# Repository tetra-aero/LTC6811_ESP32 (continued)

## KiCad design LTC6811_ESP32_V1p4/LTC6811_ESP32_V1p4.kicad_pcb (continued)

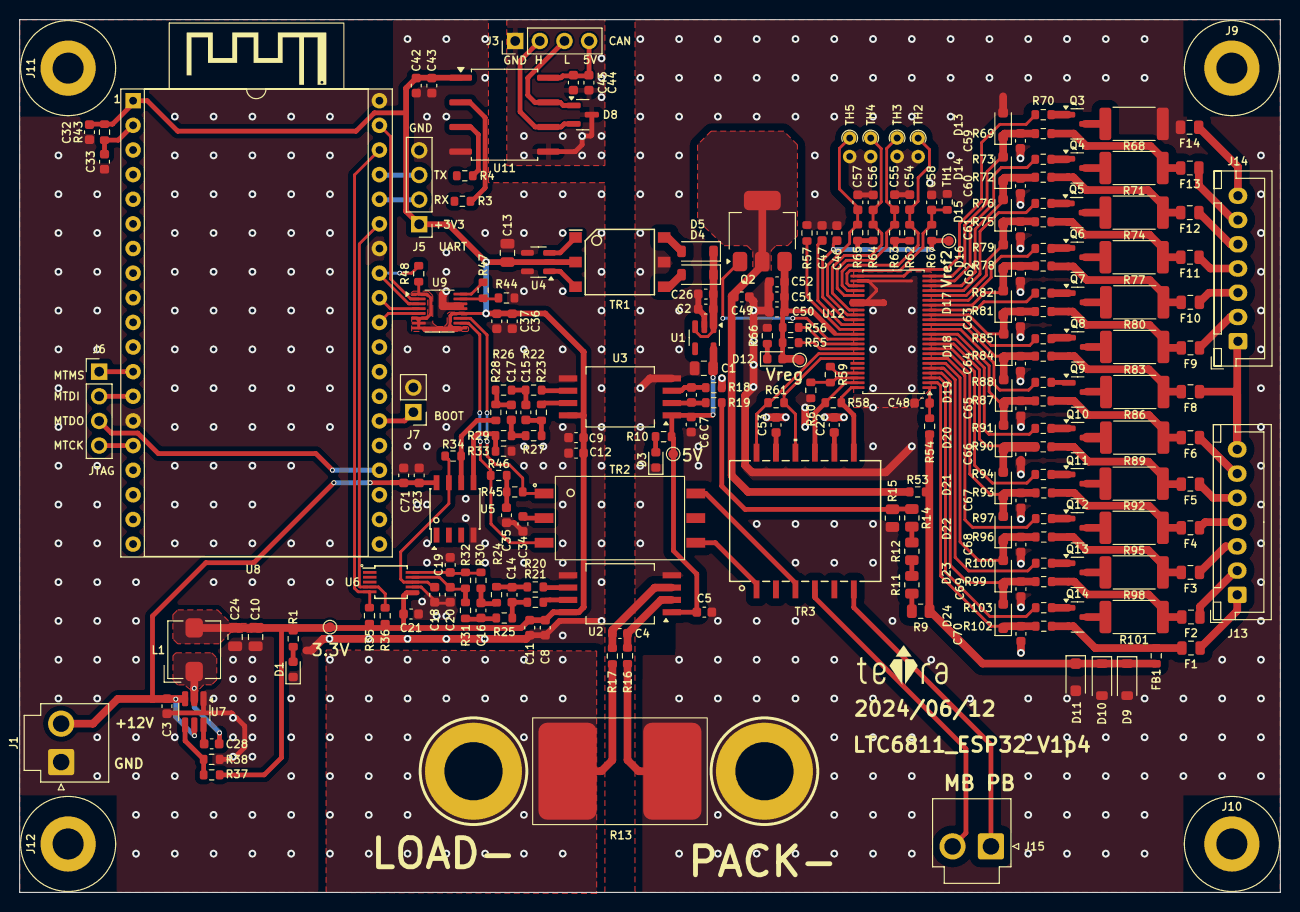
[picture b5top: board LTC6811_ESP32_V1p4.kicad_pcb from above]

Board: 2 copper layers, 130.0 x 90.0 mm, 239 parts (0 on the bottom side), 168 nets.

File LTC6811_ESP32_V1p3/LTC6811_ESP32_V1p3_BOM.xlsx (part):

LTC6811_ESP32_V1p3 BOM
 | Reference | Value | Footprint | Datasheet | Description | Link | MPN | Quantity
1 | BZ1 | AI-1027-TWT-5V | Buzzer_Beeper:Beeper_AI-1027-TWT-5V | https://www.puiaudio.com/media/SpecSheet/AI-1027-TWT-5V-2-R.pdf | Buzzers Indicator, Internally Driven Electromechanical/Magnetic 5 V 30mA 2.73kH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 | https://www.digikey.jp/en/products/detail/pui-audio-inc/AI-1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 | AI-1027-TWT-5V-2-R | 1
2 | C1, C10, C13, C24, C27 | 10uF/16V | Capacitor_SMD:C_0805_2012Metric | https://mm.digikey.com/Volume0/opasdata/d220001/medias/docus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 | 10 uF ±10% 16V Ceramic Capacitor X5R 0805 (2012 Metric) | https://www.digikey.jp/en/products/detail/samsung-electro-me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 | CL21A106KOQNNNE | 5
3 | C2, C5, C6, C8, C9, C18-C21, C23, C25, C28, C32, C33, C37, C40, C48, C49, C54-C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 | 100nF/100V | Capacitor_SMD:C_0603_1608Metric | https://www.digikey.jp/en/products/detail/samsung-electro-me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 | 0.1 uF ±10% 100V Ceramic Capacitor X7R 0603 (1608 Metric) | https://www.digikey.jp/en/products/detail/samsung-electro-me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 | CL10B104KC8NNNC | 35
4 | C3, C11, C12, C38, C41 | 2.2uF/25V | Capacitor_SMD:C_0603_1608Metric | https://search.murata.co.jp/Ceramy/image/img/A01X/G101/ENG/G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 | 2.2 uF ±10% 25V Ceramic Capacitor X5R 0603 (1608 Metric) | https://www.digikey.jp/en/products/detail/murata-electronics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 | GRM188R61E225KA12D | 5
5 | C4, C7 | 330pF/100V | Capacitor_SMD:C_0603_1608Metric | https://datasheets.kyocera-avx.com/KGM_X7R.pdf | 330 pF ±10% 100V Ceramic Capacitor X7R 0603 (1608 Metric) | https://www.digikey.jp/en/products/detail/kyocera-avx/KGM15A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 | GRM188R72A331KA01D | 2
6 | C14, C15 | 2.2nF/16V | Capacitor_SMD:C_0603_1608Metric | https://connect.kemet.com:7667/gateway/IntelliData-Component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 | 2200 pF ±10% 16V Ceramic Capacitor X7R 0603 (1608 Metric) | https://www.digikey.jp/en/products/detail/kemet/C0603C222K4R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 | C0603C222K4RECAUTO | 2
7 | C16, C17 | 220pF/50V | Capacitor_SMD:C_0603_1608Metric | https://search.murata.co.jp/Ceramy/image/img/A01X/G101/ENG/G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 | 220 pF ±5% 50V Ceramic Capacitor C0G, NP0 0603 (1608 Metric) | https://www.digikey.jp/en/products/detail/murata-electronics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 | GCM1885C1H221JA16D | 2
8 | C22, C53 | 100pF/100V | Capacitor_SMD:C_0603_1608Metric | https://search.murata.co.jp/Ceramy/image/img/A01X/G101/ENG/G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 | 100 pF ±10% 100V Ceramic Capacitor X7R 0603 (1608 Metric) | https://www.digikey.jp/en/products/detail/murata-electronics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 | 0603B101K101SD | 2
9 | C26, C39 | 4.7uF/16V | Capacitor_SMD:C_0603_1608Metric | https://mm.digikey.com/Volume0/opasdata/d220001/medias/docus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 | 4.7 uF ±10% 16V Ceramic Capacitor X5R 0603 (1608 Metric) | https://www.digikey.jp/en/products/detail/samsung-electro-me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 | CL10A475KO8NNNC | 2
10 | C34, C35 | 10nF/100V | Capacitor_SMD:C_0603_1608Metric | https://search.murata.co.jp/Ceramy/image/img/A01X/G101/ENG/G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 | 10000 pF ±10% 100V Ceramic Capacitor X7R 0603 (1608 Metric) | https://www.digikey.jp/en/products/detail/murata-electronics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 | GCM188R72A103KA37D | 2
11 | C36, C46, C47, C50-C52, C71 | 1uF/25V | Capacitor_SMD:C_0603_1608Metric | https://mm.digikey.com/Volume0/opasdata/d220001/medias/docus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 | 1 uF ±10% 25V Ceramic Capacitor X7R 0603 (1608 Metric) | https://www.digikey.jp/en/products/detail/samsung-electro-me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 | 0603B105K250XD | 7
12 | D1-D3, D12 | LED Red | LED_SMD:LED_0603_1608Metric | https://optoelectronics.liteon.com/upload/download/DS-22-99-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 | Red 631nm LED Indication - Discrete 2V 0603 (1608 Metric) | https://www.digikey.jp/en/products/detail/liteon/LTST-C190KR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 | LTST-C190KRKT | 4
13 | D4, D5 | MBR0520 | Diode_SMD:D_SOD-123 | http://www.mccsemi.com/up_pdf/MBR0520~MBR0580(SOD123).pdf | Diode 20 V 500mA Surface Mount SOD-123 | https://www.digikey.jp/en/products/detail/micro-commercial-c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 | MBR0520-TP | 2
14 | D7 | ESD24VS2U | Package_TO_SOT_SMD:SOT-23 | https://www.infineon.com/dgdl/Infineon-ESD24VS2U-DS-v01_01-e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 | 41V Clamp 5A (8/20us) Ipp Tvs Diode Surface Mount PG-SOT23 | https://www.digikey.jp/en/products/detail/infineon-technolog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 | ESD24VS2UE6327HTSA1 | 1
15 | D9, D10 | 1N4148W | Diode_SMD:D_SOD-123 | https://www.diodes.com/assets/Datasheets/BAV16W_1N4148W.pdf | Diode 100 V 300mA Surface Mount SOD-123 | https://www.digikey.jp/en/products/detail/diodes-incorporate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 | 1N4148W-7-F | 2
16 | D11 | BZT52H-C62 | Diode_SMD:D_SOD-123F | https://assets.nexperia.com/documents/data-sheet/BZT52H_SER.pdf | Zener Diode 62 V 375 mW ±5% Surface Mount SOD-123F | https://www.digikey.jp/en/products/detail/nexperia-usa-inc/B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 | BZT52H-C62,115 | 1
17 | D13-D24 | PDZ7.5B | Diode_SMD:D_SOD-323_HandSoldering | https://assets.nexperia.com/documents/data-sheet/PDZ-B_SER.pdf | Zener Diode 7.6 V 400 mW ±2% Surface Mount SOD-323 | https://www.digikey.jp/en/products/detail/nexperia-usa-inc/P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 | PDZ7.5BZ | 12
18 | F1-F6, F8-F14 | MPZ2012S102ATD25 | Fuse:Fuse_0805_2012Metric | https://product.tdk.com/en/system/files?file=dam/doc/product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 | 1 kOhms @ 100 MHz 1 Power Line Ferrite Bead 0805 (2012 Metric) 1.5A 150mOhm | https://www.digikey.jp/en/products/detail/tdk-corporation/MP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 | MPZ2012S102ATD25 | 13
19 | FB1 | BLM18PG330SN1D | Resistor_SMD:R_0603_1608Metric | https://www.murata.com/en-us/products/productdata/8796738650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 | 33 Ohms @ 100 MHz 1 Power Line Ferrite Bead 0603 (1608 Metric) 3A 25mOhm | https://www.digikey.jp/en/products/detail/murata-electronics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 | BLM18PG330SN1D | 1
20 | J1, J15 | PB MB | Connector_JST:JST_VH_B2P-VH-B_1x02_P3.96mm_Vertical | https://www.jst-mfg.com/product/pdf/eng/eVH.pdf | Connector Header Through Hole 2 position 0.156" (3.96mm) | https://www.digikey.jp/en/products/detail/jst-sales-america-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 | B2P-VH | 2
21 | J4 | USB | Connector_USB:Micro_USB_B-2013499-1 | chrome-extension://efaidnbmnnnibpcajpcglclefindmkaj/https://www.te.com/usa-en/p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 | USB - micro B USB 2.0 Receptacle Connector 5 Position Surface Mount, Right Angl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 | https://www.digikey.jp/en/products/detail/te-connectivity-am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 | 2013499-1 | 1
22 | J13, J14 | B7B-XH-A | Connector_JST:JST_XH_B7B-XH-A_1x07_P2.50mm_Vertical_BAT_6S | https://www.jst-mfg.com/product/pdf/eng/eXH.pdf | Connector Header Through Hole 7 position 0.098" (2.50mm) | https://www.digikey.jp/en/products/detail/jst-sales-america-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 | B7B-XH-A | 2
23 | L1 | 3.3uH | Inductor_SMD:L_Bourns_SRP5030T | https://www.bourns.com/docs/Product-Datasheets/SRP5030CC.pdf | 3.3 uH Shielded Wirewound Inductor 5 A 38mOhm Max Nonstandard | https://www.digikey.jp/en/products/detail/bourns-inc/SRP5030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 | SRP5030CC-3R3M | 1
24 | Q1 | BSS138 | Package_TO_SOT_SMD:SOT-23 | https://mm.digikey.com/Volume0/opasdata/d220001/medias/docus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 | N-Channel 50 V 220mA (Ta) 350mW (Ta) Surface Mount SOT-23 | https://www.digikey.jp/en/products/detail/anbon-semiconducto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 | BSS138 | 1
25 | Q2 | NSV1C201MZ4 | Package_TO_SOT_SMD:SOT-223 | https://www.onsemi.com/pdf/datasheet/nss1c201mz4-d.pdf | Bipolar (BJT) Transistor NPN 100 V 2 A 100MHz 800 mW Surface Mount SOT-223 (TO-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 | https://www.digikey.jp/en/products/detail/onsemi/NSV1C201MZ4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 | NSV1C201MZ4T1G | 1
26 | Q3-Q14 | TSM2323 | Package_TO_SOT_SMD:SOT-23 | https://www.taiwansemi.com/assets/uploads/datasheet/TSM2323_F15.pdf | P-Channel 20 V 4.7A (Ta) 1.25W (Ta) Surface Mount SOT-23 | https://www.digikey.jp/en/products/detail/taiwan-semiconduct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 | TSM2323CX RFG | 12
27 | R1, R2, R10 | 470R | Resistor_SMD:R_0603_1608Metric | https://www.yageo.com/upload/media/product/products/datashee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 | 470 Ohms ±5% 0.1W, 1/10W Chip Resistor 0603 (1608 Metric) Moisture Resistant Th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 | https://www.digikey.jp/en/products/detail/yageo/RC0603JR-074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 | RC0603JR-07470RL | 3
28 | R5 | 1.5K | Resistor_SMD:R_0603_1608Metric | https://www.yageo.com/upload/media/product/products/datashee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 | 1.5 kOhms ±5% 0.1W, 1/10W Chip Resistor 0603 (1608 Metric) Moisture Resistant T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 | https://www.digikey.jp/en/products/detail/yageo/RC0603JR-071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 | RC0603JR-071K5L | 1
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
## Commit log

2023-11-14 Add daisy chain connection interface.
2023-11-15 checked bom
    checked bom
2023-11-16 check pcb size
    check pcb size
2023-11-17 Substitute components in the bom that are out of stock.
2023-11-17 Add files via upload
    I have replaced the components in the BOM purchase links that were either out of stock or temporarily available but discontinued by the manufacturer.
2023-11-30 Create LTC6811_ESP32_V1
    Update component packaging for electronic parts and add master-slave board connection interfaces.
2023-11-30 Update LTC6811_ESP32_V1
2023-11-30 Rename LTC6811_ESP32.kicad_pcb to LTC6811_ESP32_v1/LTC6811_ESP32.kicad_pcb
2023-11-30 Add master-slave board connection interfaces
    Update component packaging for electronic parts and add master-slave board connection interfaces.
2023-11-30 Rename LTC6811_ESP32.kicad_pcb to LTC6811_ESP32.kicad_pcb
2023-11-30 Rename LTC6811_ESP32.kicad_prl to LTC6811_ESP32_V0 /LTC6811_ESP32.kicad_prl
2023-11-30 Rename LTC6811_ESP32.kicad_pro to LTC6811_ESP32_V0 /LTC6811_ESP32.kicad_pro
2023-11-30 Rename LTC6811_ESP32.kicad_prl to LTC6811_ESP32.kicad_prl
2023-11-30 Rename LTC6811_ESP32.kicad_pro to LTC6811_ESP32.kicad_pro
2023-11-30 Rename LTC6811_ESP32_BOM.xlsx to LTC6811_ESP32_V0/LTC6811_ESP32_BOM.xlsx
2023-11-30 Rename LTC6811_ESP32_Library.pretty.rar to LTC6811_ESP32_V0/LTC6811_ESP32_Library.pretty.rar
2023-11-30 Rename LTC6811_ESP32_V1_BOM.xlsx to LTC6811_ESP32_V1.0_BOM.xlsx
2023-12-13 Optimize Isolated Power Supply Circuit
2024-02-13 Rename LTC6811_ESP32_V1.2.kicad_pro to LTC6811_ESP32_V1.2/LTC6811_ESP32_V1.2.kicad_pro
2024-02-20 finished
2024-02-21 add BOM
2024-02-21 Rename LTC6811_ESP32_V1.0.F.png to LTC6811_ESP32_V1.0.F.png
2024-02-21 Rename LTC6811_ESP32_V1.0.kicad_pro to LTC6811_ESP32_V1.0.kicad_pro
2024-02-21 Rename LTC6811_ESP32_V1.0_BOM.xlsx to LTC6811_ESP32_V1.0_BOM.xlsx
2024-02-21 Rename LTC6811_ESP32_V1_Library.pretty.rar to LTC6811_ESP32_V1_Library.pretty.rar
2024-02-22 Rename LTC6811_ESP32_V1p2.kicad_pro to LTC6811_ESP32_V1p2/LTC6811_ESP32_V1p2.kicad_pro
2024-02-24 fix thermal lilef
    fix thermal lilef
2024-02-24 add ignore gerber
    add ignore gerber
2024-03-21 Optimize signal transmission lines.
2024-03-29 Synchronize library files
    The default library files have been restored to KiCad-7.0.11, and DRC check has passed.
2024-03-29 V1p31 Synchronize library files
    The default library files have been restored to KiCad-7.0.11, and DRC check has passed.
2024-03-29 Rename LTC6811_ESP32_V1p31.kicad_pro to LTC6811_ESP32_V1p31.kicad_pro
2024-06-01 change page setting A3 for print
    change page setting A3 for print
2024-06-12 Replace out-of-stock components
2024-06-12 kicad v8対応
    kicad v8対応
2024-06-18 Rename ESP32_Master.kicad_prl to ESP32_Master.kicad_prl
2024-06-18 update name ESP32_Master_V0
2024-07-02 add license
    add license
2024-07-11 Corrected the problem of USB and CAN sharing TXRX
2024-08-05 Add 8P DIP switch and mcp23s17
2024-08-06 Add two positioning holes.
2024-08-06 BMS for 96 cells
2024-08-07 Update BOM
2024-09-12 fix around CAN IC
    fix around CAN IC
2024-09-12 fix page number
    fix page number
2024-11-01 Connect 5V and correct GND
2024-11-01 rename sub V5 step
    rename sub V5 step
2025-11-14 Add 3 new relay control interface
